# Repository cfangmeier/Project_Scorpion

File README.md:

Project_Scorpion
================

Code repository for the Project Scorpion smart liquor cabinet project

The barcode scanner requires the following udev rule:

SUBSYSTEM=="input", ATTRS{idVendor}=="1d57", ATTRS{idProduct}=="001c" MODE="0644"

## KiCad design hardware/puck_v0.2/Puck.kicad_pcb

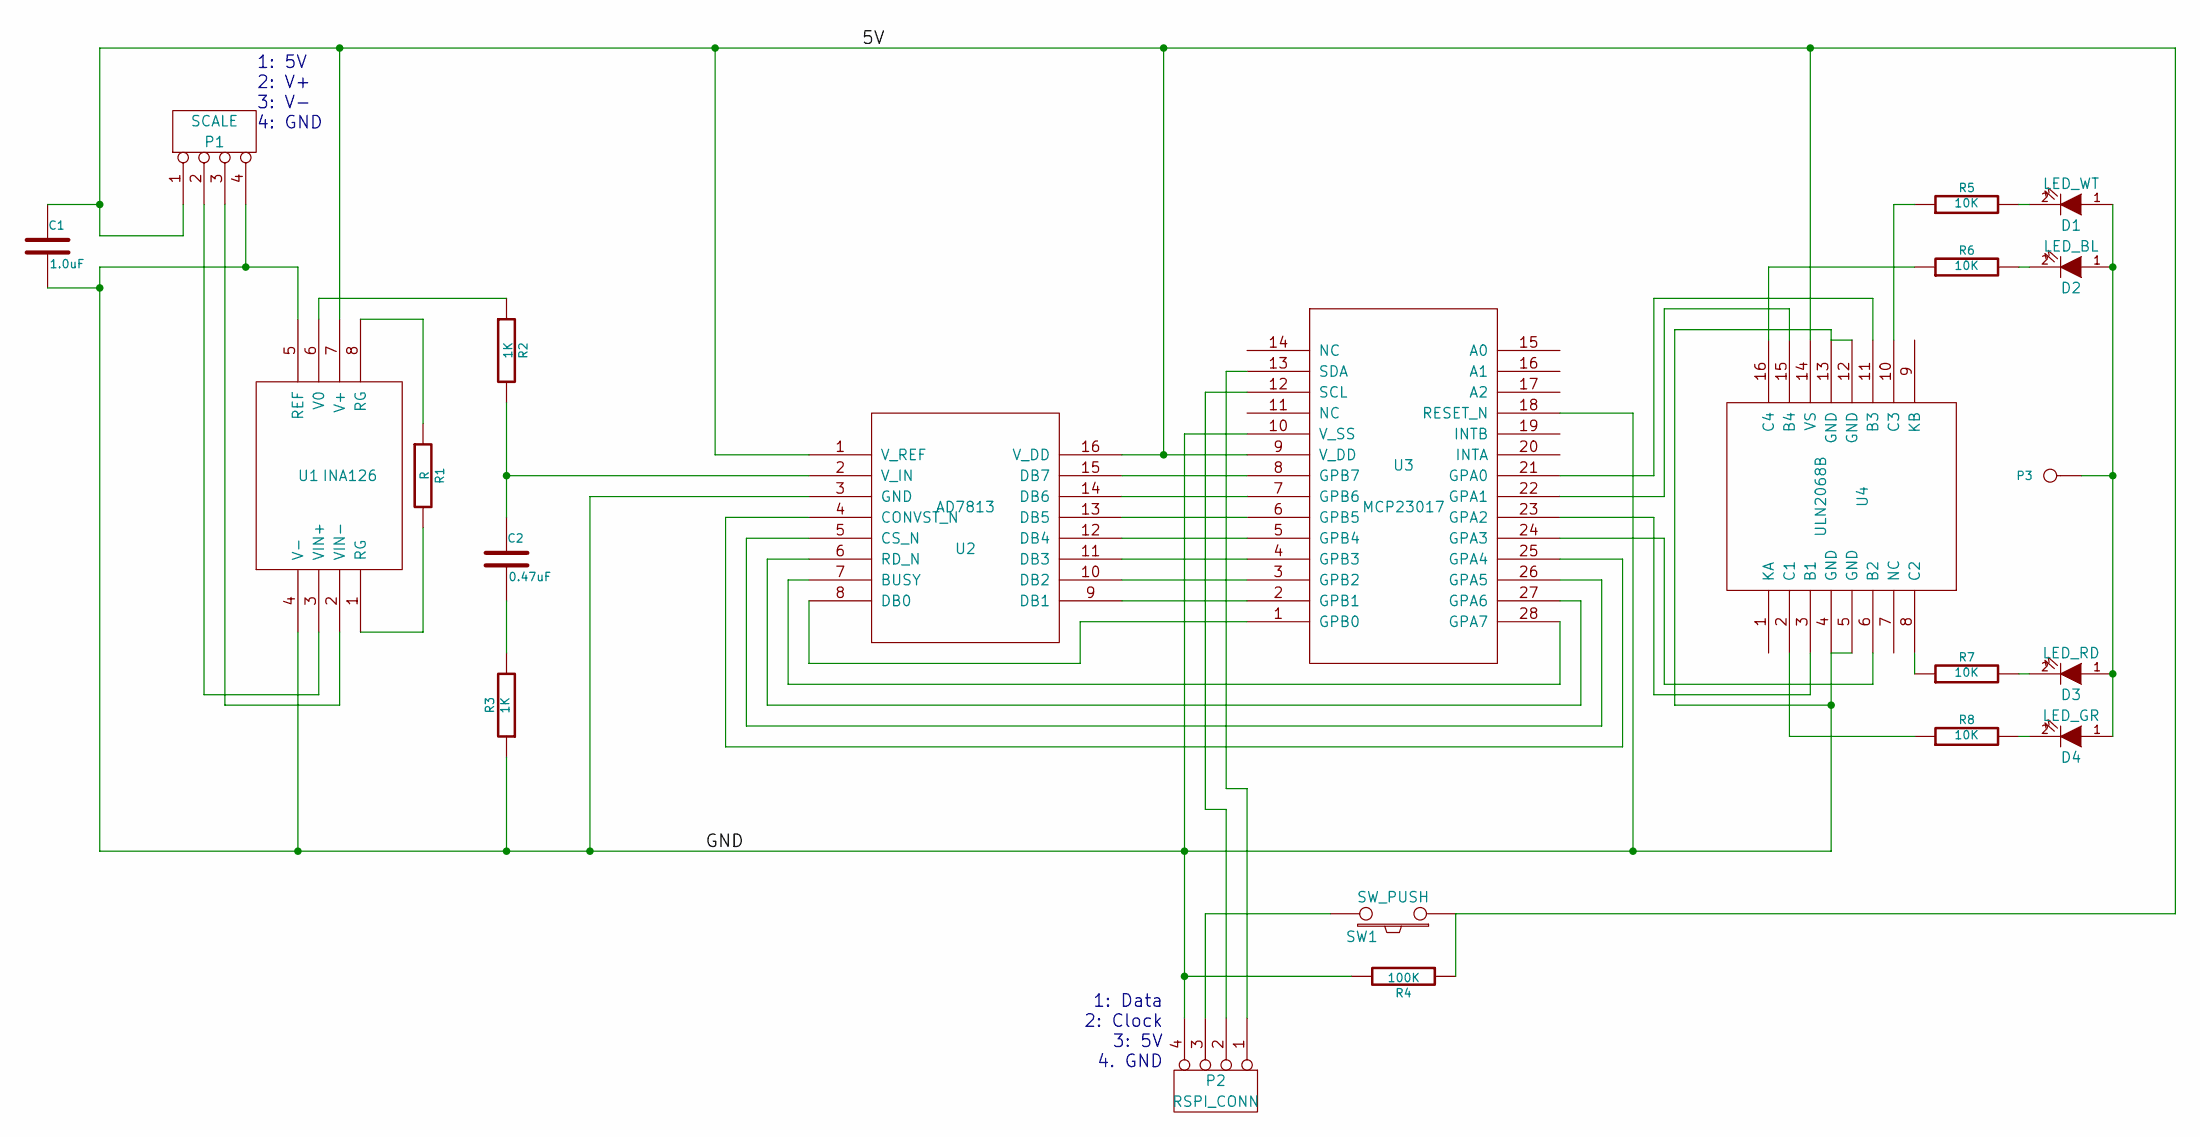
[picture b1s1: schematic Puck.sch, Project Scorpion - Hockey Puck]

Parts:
C1: 1.0uF
C2: 0.47uF
D1: LED_WT
D2: LED_BL
D3: LED_RD
D4: LED_GR
P1: SCALE
P2: RSPI_CONN
P3: 5V_LED
R1: R
R2, R3: 1K
R4: 100K
R5, R6, R7, R8: 10K
SW1: SW_PUSH
U1: INA126; MODULE
U2: AD7813; MODULE
U3: MCP23017; MODULE
U4: ULN2068B; MODULE

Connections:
/5V: C1.1, P1.1, R4.1, SW1.1, U1.7 (V+), U2.1 (V_REF), U2.16 (V_DD), U3.9 (V_DD), U4.14 (VS)
/GND: C1.2, P1.4, P2.4, R3.1, R4.2, U1.4 (V-), U1.5 (REF), U2.3 (GND), U3.10 (V_SS), U3.18 (RESET_N), U4.4 (GND), U4.5 (GND), U4.12 (GND), U4.13 (GND)
unnamed: R5.1, U4.10 (C3)
unnamed: P2.2, U3.12 (SCL)
unnamed: R7.1, U4.8 (C2)
unnamed: U3.21 (GPA0), U4.11 (B3)
unnamed: D4.2 (K), R8.2
unnamed: P2.3, SW1.2
unnamed: R6.1, U4.16 (C4)
unnamed: D1.2 (K), R5.2
unnamed: R8.1, U4.2 (C1)
unnamed: U3.23 (GPA2), U4.3 (B1)
unnamed: P1.3, U1.2 (VIN-)
unnamed: R1.2, U1.1 (RG)
unnamed: R1.1, U1.8 (RG)
unnamed: R2.1, U1.6 (V0)
unnamed: P1.2, U1.3 (VIN+)
unnamed: C2.2, R3.2
unnamed: D1.1 (A), D2.1 (A), D3.1 (A), D4.1 (A), P3.1
unnamed: D2.2 (K), R6.2
unnamed: D3.2 (K), R7.2
unnamed: P2.1, U3.13 (SDA)
unnamed: U3.24 (GPA3), U4.6 (B2)
unnamed: U2.4 (CONVST_N), U3.25 (GPA4)
unnamed: C2.1, R2.2, U2.2 (V_IN)
unnamed: U2.5 (CS_N), U3.26 (GPA5)
unnamed: U2.7 (BUSY), U3.28 (GPA7)
unnamed: U2.9 (DB1), U3.2 (GPB1)
unnamed: U2.10 (DB2), U3.3 (GPB2)
unnamed: U2.11 (DB3), U3.4 (GPB3)
unnamed: U2.12 (DB4), U3.5 (GPB4)
unnamed: U2.13 (DB5), U3.6 (GPB5)
unnamed: U2.14 (DB6), U3.7 (GPB6)
unnamed: U2.15 (DB7), U3.8 (GPB7)
unnamed: U2.6 (RD_N), U3.27 (GPA6)
unnamed: U3.22 (GPA1), U4.15 (B4)
unnamed: U2.8 (DB0), U3.1 (GPB0)

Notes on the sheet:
1: Data 2: Clock 3: 5V 4. GND
1: 5V 2: V+ 3: V- 4: GND

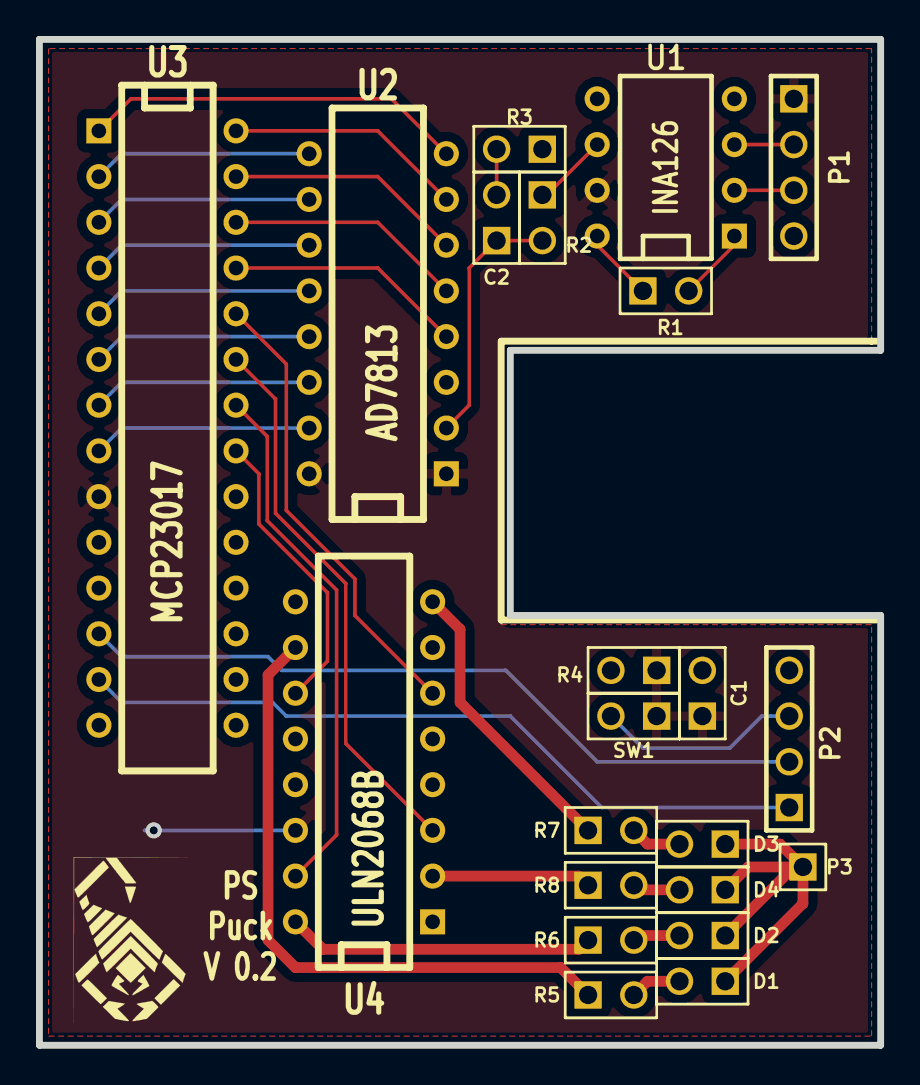
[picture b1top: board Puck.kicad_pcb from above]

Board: 2 copper layers, 46.7 x 55.9 mm, 23 parts (0 on the bottom side), 37 nets.

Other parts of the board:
VAL: primary_logo

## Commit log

2013-12-13 didn't do nothing
2014-02-09 Create some code packaging structure. Add code to do UPC lookups. UPC access key is stored in non-committed configuration file.
2014-02-10 Add current state of Puck code, including the Adafruit interface code.
2014-02-13 Fix indentation in Adafruit_MCP230xx Remove testing code from hal.Puck; create appropriate interface. Remove sqlite3 code from db.(replace with sqlalchemy) removed upclookup. add dbobjects which defi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
2014-02-15 Add config file. Rename Puck.py to puck.py to adhere to naming convention for modules. Add code to read barcode scanner. Add some basic db code.
2014-02-17 fix import in puck. refactor scanner to run asynchronously add LiquorSKU and GenLiquorIngredient to dbobjects introduce default_data human editable xml file create xmlparser to parse afformentioned f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
2014-02-18 sample push
2014-02-18 Create gh-pages branch via GitHub
2014-02-18 small update to main
2014-02-19 add puck info to config fix pin numbers in puck keep list of pucks in puck scanner_data is now a field in the scanner module add some methods in db to get objects from db add puck_address as field in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
2014-02-19 continue filling out command functionality. still remaining: input new bottle. change puck address in config from string to int add kill_light macro in puck to turn off all lights. add logic for cons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
2014-02-21 remove sample.txt fix field name error in command update xml_path to run from main prevent error with invalid puck addresses allow scanner thread to be stopped properly upon shutdown add some invento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
2014-02-21 move adafruit code to adafruit package parallel to scorpion. compartmentalize scanner threading code to threading, giving it a purely functional interface. remove brand field from Extra object. add a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
2014-02-23 Some bugfixes to run in the pi
2014-02-23 add command to scan in new bottle. add some new getter functions in db.
2014-03-02 Begin switching from the print statement to the more flexible print function from python 3.
2014-03-03 Made changes to be python3 compatible. We should probably switch to python3 for this project see: https://wiki.python.org/moin/Python2orPython3
2014-03-24 More python3 fixes.
2014-03-24 fix formatting in Adafruit_I2C fix crash when adding new bottle that already exists in db.
2014-03-27 Initial commit with UI(kivy) code. more to come:)
2014-03-28 Add some more more kivy code to match the ui mockups. Very much a work in progress.
2014-03-29 Basic layout of ui complete. move some files around.
2014-03-29 Add date_added field to liquor_inventory. UI additions.
2014-03-30 Add some ReStructuredText fields for display of things like description and mixing instructions. Begin extracting data fields from screen widgets. (more to be done here)
2014-04-01 Add DrinkSelectScreen to ui. update method override style.
2014-04-01 mostly add hookups between ui and data.
2014-04-02 add measure_unit field to ingredients. add image field to thing needing pictures made puck_address a unique column
2014-04-17 Add functionality to get available puck address changed many fields in db to not nullable Begin adding screens needed to add a new bottle.
2014-04-18 Continue to implement add-liquor screens.
2014-04-21 Finished adding screens to add new liquor to inventory. Next: Add new drinks.
2014-04-22 hooked up barcode scanner to gui
2014-04-23 Refactor UI code to be more kivy-ish. Mostly switching from function calls to properties. (Which I finally understand.)
2014-05-06 Added some coloring. It's super classy. ;)
2014-05-08 Shuffleing code around. This is Broken.
2014-05-15 Finished some major refactoring of ui code.
2014-05-21 Inserted first use of a shader **faaaaaaannncy**
    Added some pictures for saturday mixing session.
2014-05-23 Add more drink images. Fix fancy texture on main screens. Begin migration from xml to custom default-data format.
2014-05-25 Progress on .dat parser. Currently broken.
2014-05-25 Finish transition to custom data parser.
2014-05-25 Removed description fields. Adds very little to interface and I'm too lazy to fill them out.
2014-05-26 Finished adding drinks from the first mixing session to the default.dat file.
2014-06-01 Add hardware(Puck V0.2) into version control.
2015-01-26 Begin Version 1.0 of Puck Electronics
2015-07-06 adds version 2 of the puck
2015-07-12 fixes working point of amplifier circuit in puck v2
